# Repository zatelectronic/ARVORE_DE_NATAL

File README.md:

# ÁRVORE DE NATAL — shield de LEDs para Arduino UNO

Uma árvore de Natal desenhada na serigrafia com **12 LEDs vermelhos** de 5 mm que viram as bolinhas da árvore. A placa encaixa como **shield no Arduino UNO R3** (barra digital D2–D13 + GND) e cada LED é um pino do Arduino.

## Funcionalidades

- ✅ **Shield Arduino UNO R3** (A1) — só a barra digital D2–D13 + GND (não usa 5 V, 3,3 V nem analógicos)
- ✅ **12 LEDs 5 mm vermelhos** THT (D1–D12), um por pino digital
- ✅ **12 resistores 220 Ω 1/4 W** axiais (R1–R12), um por LED
- ✅ **Arte na serigrafia** recortada em volta de cada LED (nada de tinta sobre pad)
- ✅ Placa **100 × 100 mm**, 2 camadas, plano de GND nas duas faces

## Ligação dos LEDs

| LED | Cor | Resistor | Pino do Arduino | Corrente @ 5 V |
|---|---|---|---|---|
| D1 | vermelho | R1 220 Ω | D2 | ≈ 13,6 mA |
| D2 | vermelho | R2 220 Ω | D3 | ≈ 13,6 mA |
| D3 | vermelho | R3 220 Ω | D4 | ≈ 13,6 mA |
| D4 | vermelho | R4 220 Ω | D5 | ≈ 13,6 mA |
| D5 | vermelho | R5 220 Ω | D6 | ≈ 13,6 mA |
| D6 | vermelho | R6 220 Ω | D7 | ≈ 13,6 mA |
| D7 | vermelho | R7 220 Ω | D8 | ≈ 13,6 mA |
| D8 | vermelho | R8 220 Ω | D9 | ≈ 13,6 mA |
| D9 | vermelho | R9 220 Ω | D10 | ≈ 13,6 mA |
| D10 | vermelho | R10 220 Ω | D11 | ≈ 13,6 mA |
| D11 | vermelho | R11 220 Ω | D12 | ≈ 13,6 mA |
| D12 | vermelho | R12 220 Ω | D13 | ≈ 13,6 mA |

Cada canal: **pino → 220 Ω → LED → GND** (nível alto acende). Todos acesos ≈ **163 mA** — dentro do limite do UNO (≈ 200 mA no total), mas evite deixar os 12 acesos por muito tempo.

## Diagrama de blocos

```
┌──────────────────────┐  ARD_D2 … ARD_D13  ┌──────────────────────────┐
│  Arduino UNO R3 (A1) │ ─────────────────► │ 12 × [220 Ω → LED 5 mm]  │
│  barra D2–D13 + GND  │ ◄──────── GND ──── │  R1–R12      D1–D12      │
└──────────────────────┘                    └──────────────────────────┘
```

## Firmware

`firmware/ARVORE_DE_NATAL/ARVORE_DE_NATAL.ino` — exemplo simples (corrida, pisca alternado e aleatório).

## Esquemático (KiCad 10)

| Pág. | Folha | Conteúdo |
|---|---|---|
| 1 | Capa (A2) | blocos, mapa dos LEDs na placa, vista 3D |
| 2 | ARDUINO | A1 (shield UNO R3) + PWR_FLAG do GND |
| 3 | LEDS | D1–D12 + R1–R12 |

## Lista de materiais

| Ref. | Qtd | Valor | Footprint |
|---|---|---|---|
| A1 | 1 | Arduino UNO R3 (encaixe) | ZAT_Board_Arduino:Uno_R3_Shield_D2-D13 |
| D1–D12 | 12 | LED 5 mm vermelho | ZAT_LED:LED_D5.0mm_Red |
| R1–R12 | 12 | 220 Ω 1/4 W | ZAT_Resistor_THT:R_Axial_DIN0204_L3.6mm_D1.6mm_P7.62mm_Horizontal_220R |

## Arquivos

- `ARVORE_DE_NATAL.kicad_pro` — projeto KiCad 10 (bibliotecas globais KiCad + ZAT, sem pasta lib)
- `Zat_TitleBlock.kicad_wks` — moldura Zat Electronic
- `packages3D/` — modelos 3D usados na vista 3D

## Licença / autor

Projeto **Zat Electronic** — Kenneth Zat · Osasco/SP · hardware aberto.

*Revisão R01 — 2026-11-12 — KiCad 10.*

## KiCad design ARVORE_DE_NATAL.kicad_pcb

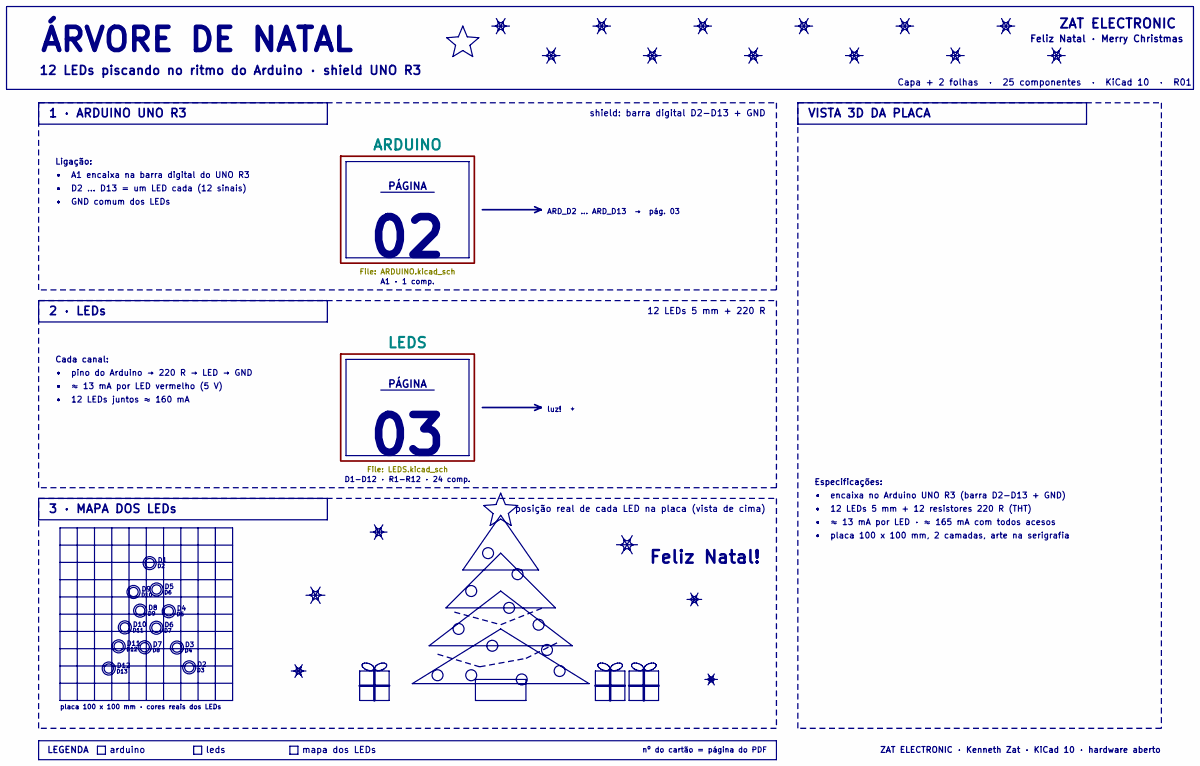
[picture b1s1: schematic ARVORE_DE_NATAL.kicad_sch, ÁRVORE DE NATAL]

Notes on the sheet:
ZAT ELECTRONIC
Especificações:
D10
ZAT ELECTRONIC · Kenneth Zat · KiCad 10 · hardware aberto
• ≈ 13 mA por LED · ≈ 165 mA com todos acesos
• 12 LEDs 5 mm + 12 resistores 220 R (THT)
1 · ARDUINO UNO R3
• D2 … D13 = um LED cada (12 sinais)
arduino
PÁGINA
nº do cartão = página do PDF
VISTA 3D DA PLACA
• ≈ 13 mA por LED vermelho (5 V)
Ligação:
D1-D12 · R1-R12 · 24 comp.
12 LEDs 5 mm + 220 R
shield: barra digital D2-D13 + GND
leds
placa 100 x 100 mm · cores reais dos LEDs
2 · LEDs
• encaixa no Arduino UNO R3 (barra D2-D13 + GND)
Capa + 2 folhas · 25 componentes · KiCad 10 · R01
Feliz Natal · Merry Christmas
• pino do Arduino → 220 R → LED → GND
D11
Cada canal:
luz! ✦
ARD_D2 … ARD_D13 → pág. 03
A1 · 1 comp.
posição real de cada LED na placa (vista de cima)
Feliz Natal!
• 12 LEDs juntos ≈ 160 mA
3 · MAPA DOS LEDs
LEGENDA
• placa 100 x 100 mm, 2 camadas, arte na serigrafia
ÁRVORE DE NATAL
mapa dos LEDs
• GND comum dos LEDs
D13
12 LEDs piscando no ritmo do Arduino · shield UNO R3

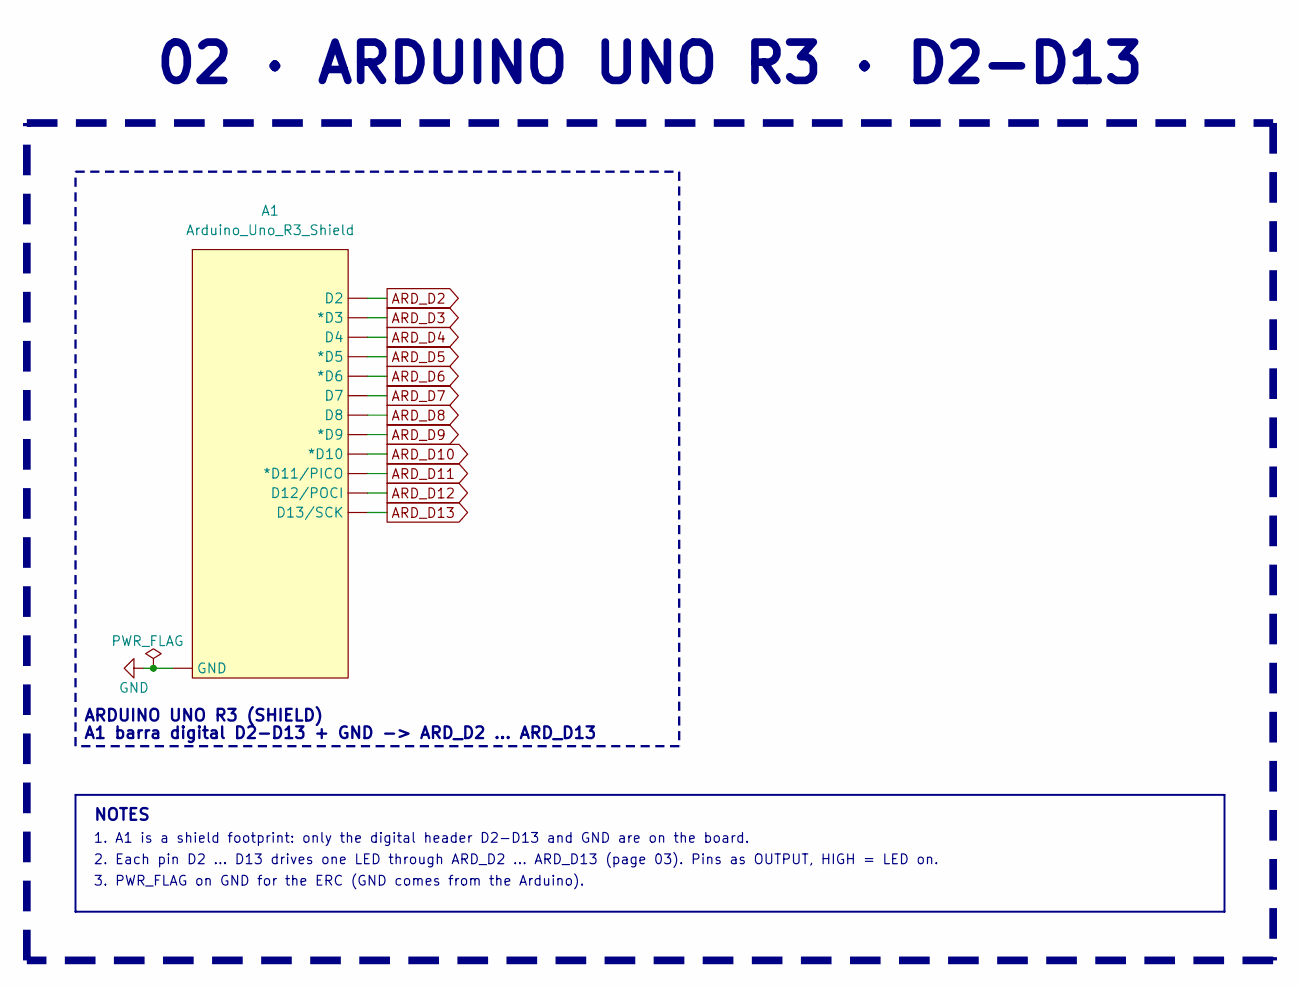
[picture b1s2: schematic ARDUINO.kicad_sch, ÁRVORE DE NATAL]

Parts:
A1: Arduino_Uno_R3_Shield; Uno_R3_Shield_D2-D13

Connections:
ARD_D2: A1.D2; also elsewhere on the board
ARD_D3: A1.D3 (*D3); also elsewhere on the board
ARD_D4: A1.D4; also elsewhere on the board
ARD_D5: A1.D5 (*D5); also elsewhere on the board
ARD_D6: A1.D6 (*D6); also elsewhere on the board
ARD_D7: A1.D7; also elsewhere on the board
ARD_D8: A1.D8; also elsewhere on the board
ARD_D9: A1.D9 (*D9); also elsewhere on the board
ARD_D10: A1.D10 (*D10); also elsewhere on the board
ARD_D11: A1.D11 (*D11/PICO); also elsewhere on the board
ARD_D12: A1.D12 (D12/POCI); also elsewhere on the board
ARD_D13: A1.D13 (D13/SCK); also elsewhere on the board
GND: A1.GND; also elsewhere on the board

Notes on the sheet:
ARDUINO UNO R3 (SHIELD)
NOTES
3. PWR_FLAG on GND for the ERC (GND comes from the Arduino).
1. A1 is a shield footprint: only the digital header D2-D13 and GND are on the board.
02 · ARDUINO UNO R3 · D2-D13
2. Each pin D2 ... D13 drives one LED through ARD_D2 ... ARD_D13 (page 03). Pins as OUTPUT, HIGH = LED on.
A1 barra digital D2-D13 + GND -> ARD_D2 ... ARD_D13

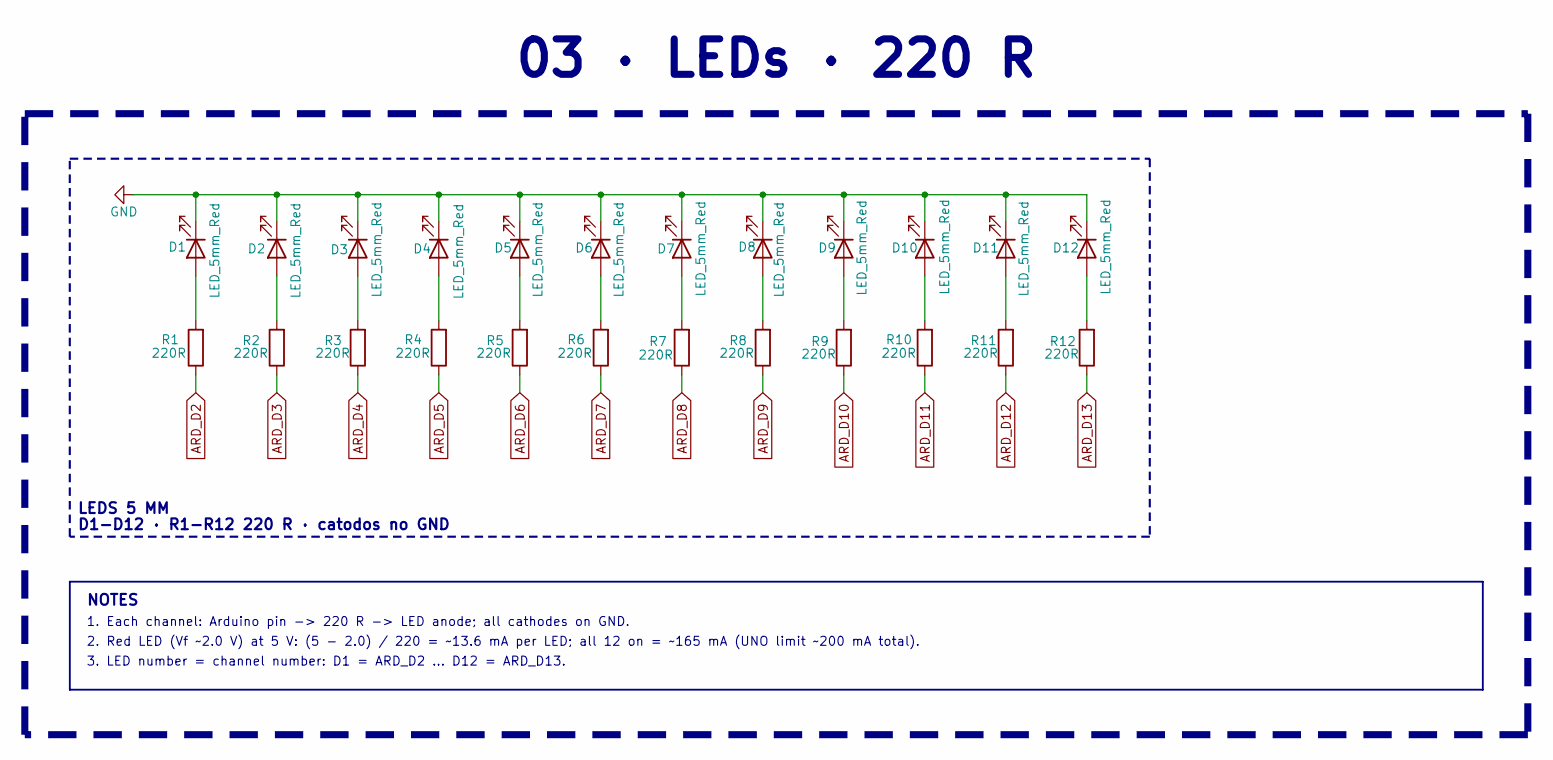
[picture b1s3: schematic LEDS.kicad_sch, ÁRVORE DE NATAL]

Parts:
D1, D2, D3, D4, D5, D6, D7, D8, D9, D10, D11, D12: LED_5mm_Red; LED_D5.0mm_Red
R1, R2, R3, R4, R5, R6, R7, R8, R9, R10, R11, R12: 220R; R_Axial_DIN0204_L3.6mm_D1.6mm_P7.62mm_Horizontal_220R

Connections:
ARD_D2: R1.1; also elsewhere on the board
ARD_D3: R2.1; also elsewhere on the board
ARD_D4: R3.1; also elsewhere on the board
ARD_D5: R4.1; also elsewhere on the board
ARD_D6: R5.1; also elsewhere on the board
ARD_D7: R6.1; also elsewhere on the board
ARD_D8: R7.1; also elsewhere on the board
ARD_D9: R8.1; also elsewhere on the board
ARD_D10: R9.1; also elsewhere on the board
ARD_D11: R10.1; also elsewhere on the board
ARD_D12: R11.1; also elsewhere on the board
ARD_D13: R12.1; also elsewhere on the board
GND: D1.1 (K), D2.1 (K), D3.1 (K), D4.1 (K), D5.1 (K), D6.1 (K), D7.1 (K), D8.1 (K), D9.1 (K), D10.1 (K), D11.1 (K), D12.1 (K); also elsewhere on the board
unnamed: D1.2 (A), R1.2
unnamed: D2.2 (A), R2.2
unnamed: D3.2 (A), R3.2
unnamed: D4.2 (A), R4.2
unnamed: D5.2 (A), R5.2
unnamed: D6.2 (A), R6.2
unnamed: D7.2 (A), R7.2
unnamed: D8.2 (A), R8.2
unnamed: D9.2 (A), R9.2
unnamed: D10.2 (A), R10.2
unnamed: D11.2 (A), R11.2
unnamed: D12.2 (A), R12.2

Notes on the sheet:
1. Each channel: Arduino pin -> 220 R -> LED anode; all cathodes on GND.
2. Red LED (Vf ~2.0 V) at 5 V: (5 - 2.0) / 220 = ~13.6 mA per LED; all 12 on = ~165 mA (UNO limit ~200 mA total).
NOTES
03 · LEDs · 220 R
D1-D12 · R1-R12 220 R · catodos no GND
3. LED number = channel number: D1 = ARD_D2 ... D12 = ARD_D13.
LEDS 5 MM

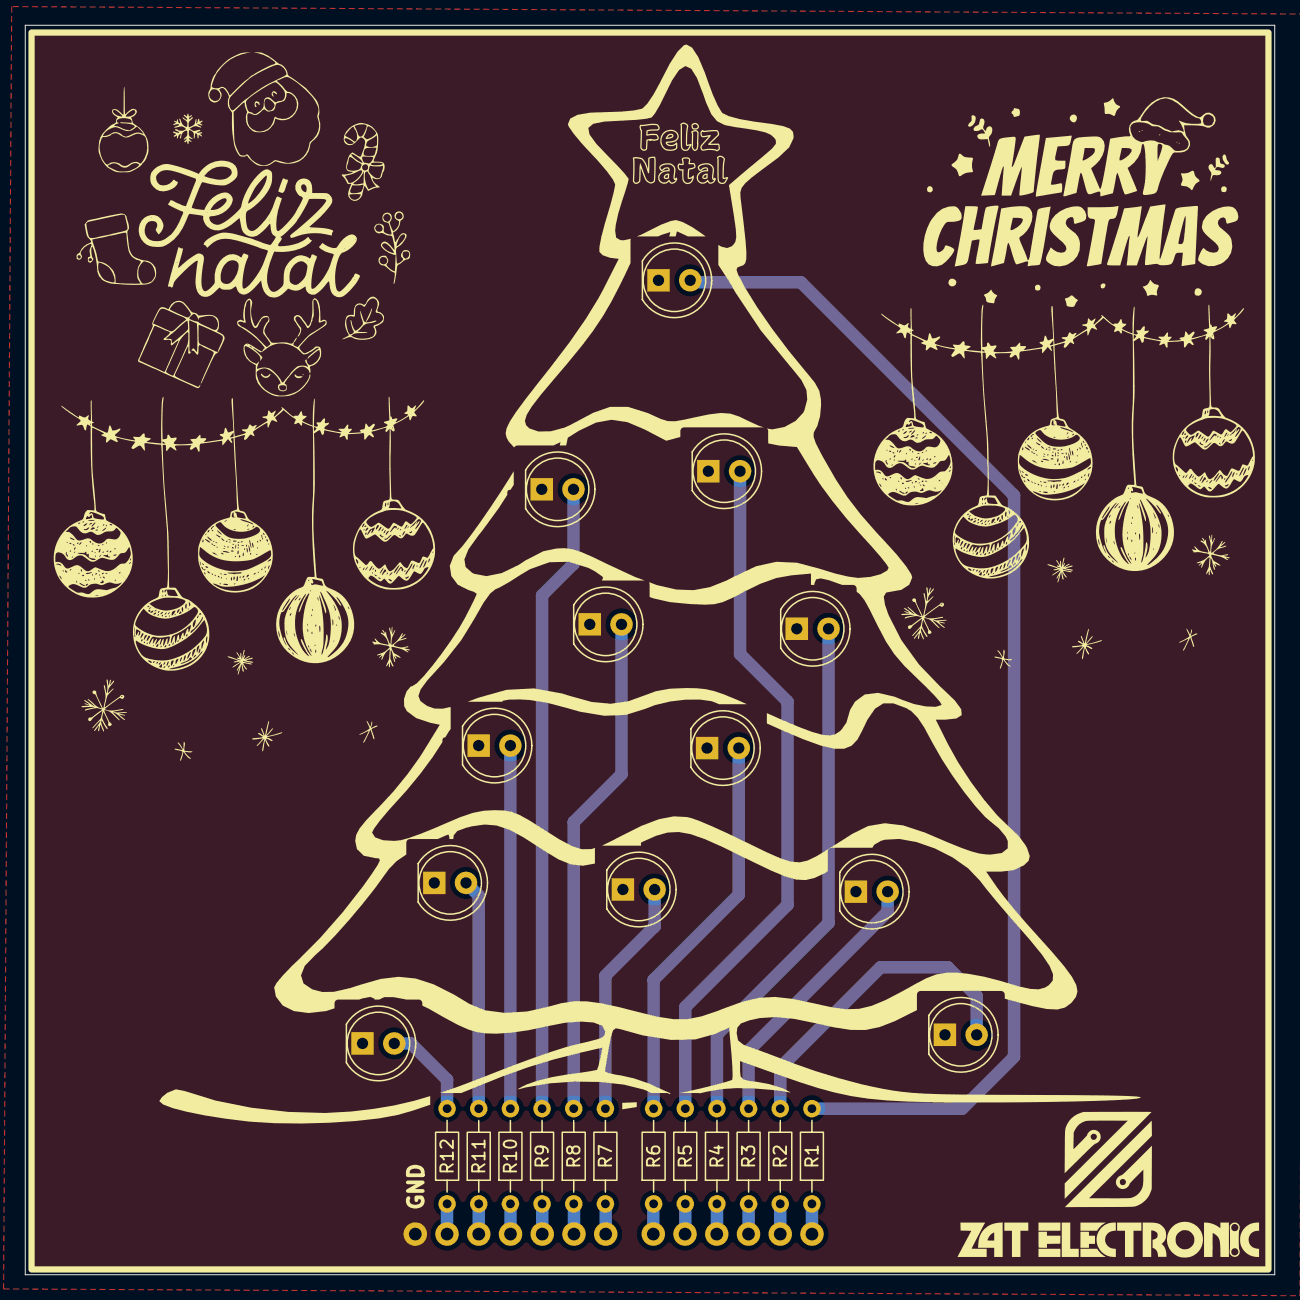
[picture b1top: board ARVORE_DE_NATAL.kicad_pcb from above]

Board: 2 copper layers, 100.0 x 100.0 mm, 25 parts (0 on the bottom side), 25 nets.

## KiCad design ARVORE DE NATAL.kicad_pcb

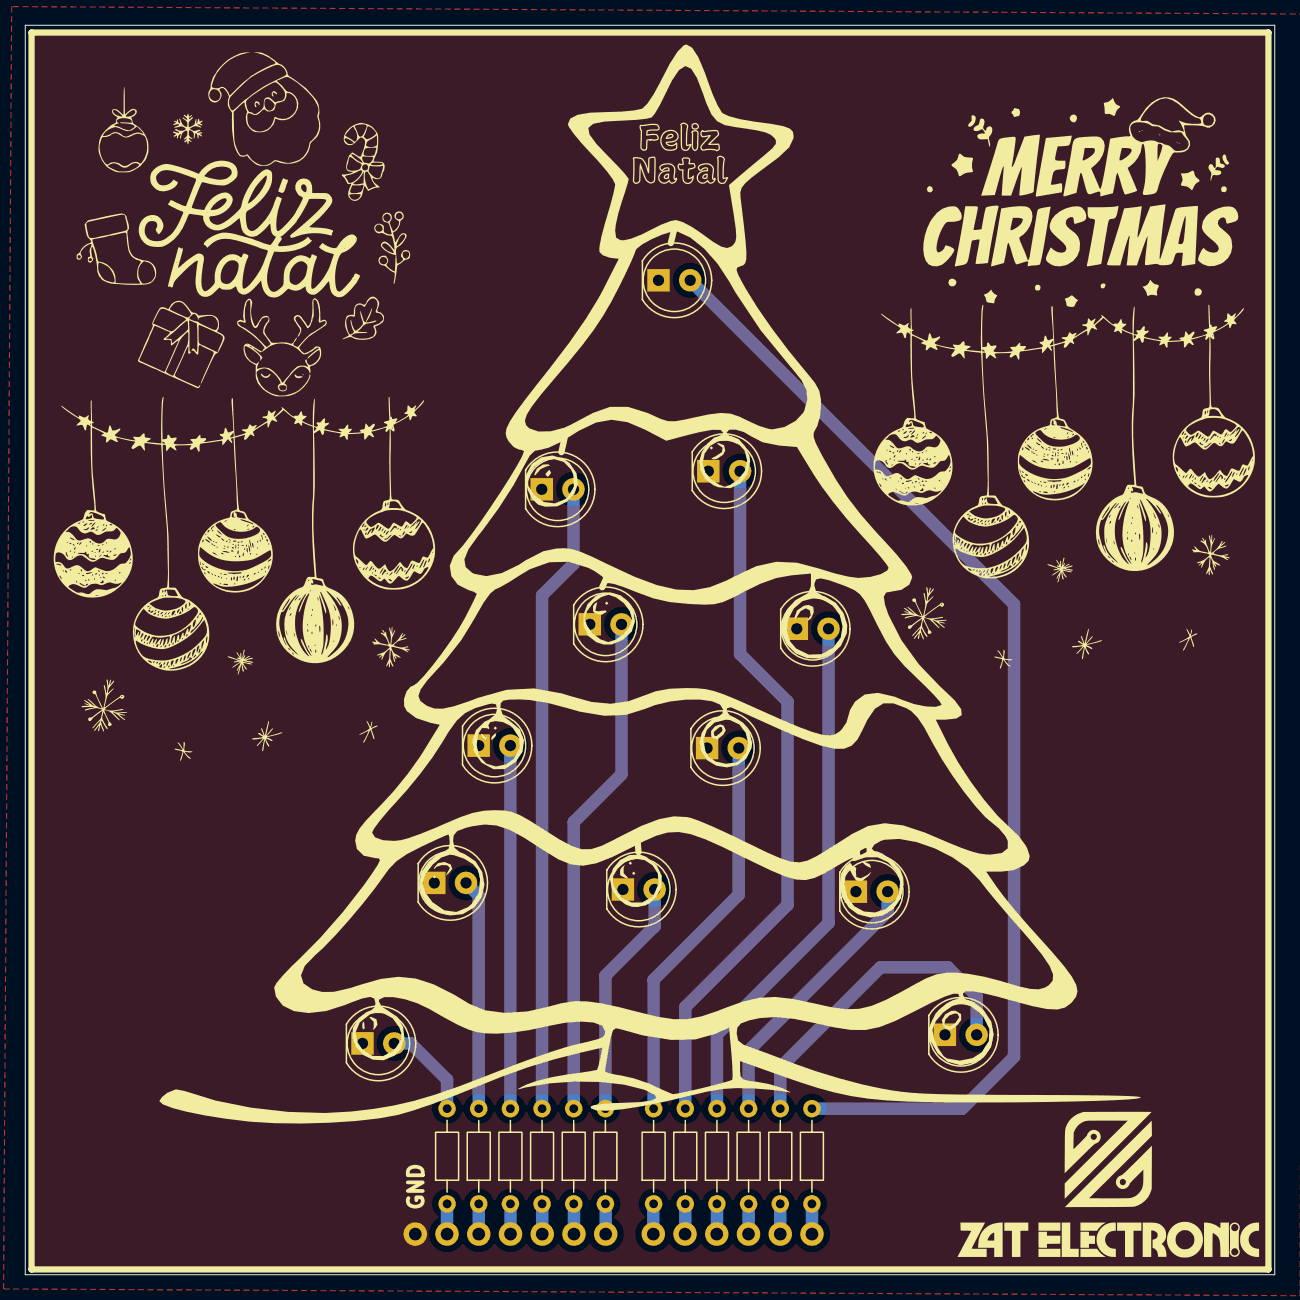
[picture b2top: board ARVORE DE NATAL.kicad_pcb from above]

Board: 2 copper layers, 100.0 x 100.0 mm, 25 parts (0 on the bottom side), 25 nets.

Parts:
B1: Arduino_Uno_R3_Shield; Uno_R3_Shield_NoLabels
L1, L2, L3, L4, L5, L6, L7, L8, L9, L10, L11, L12: LED 5MM; LED_D5.0mm
R1, R2, R3, R4, R5, R6, R7, R8, R9, R10, R11, R12: 220Ω; R_Axial_DIN0204_L3.6mm_D1.6mm_P7.62mm_Horizontal

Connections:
GND: B1.GND, L1.1 (K), L2.1 (K), L3.1 (K), L4.1 (K), L5.1 (K), L6.1 (K), L7.1 (K), L8.1 (K), L9.1 (K), L10.1 (K), L11.1 (K), L12.1 (K)
unnamed: B1.D3 (*D3), R2.1
unnamed: B1.D5 (*D5), R4.1
unnamed: B1.D6 (*D6), R5.1
unnamed: B1.D9 (*D9), R8.1
unnamed: B1.D10 (*D10), R9.1
unnamed: B1.D11 (*D11/PICO), R10.1
unnamed: B1.D12 (D12/POCI), R11.1
unnamed: B1.D13 (D13/SCK), R12.1
unnamed: B1.D2, R1.1
unnamed: B1.D4, R3.1
unnamed: B1.D7, R6.1
unnamed: B1.D8, R7.1
unnamed: L1.2 (A), R1.2
unnamed: L2.2 (A), R2.2
unnamed: L3.2 (A), R3.2
unnamed: L4.2 (A), R4.2
unnamed: L5.2 (A), R5.2
unnamed: L6.2 (A), R6.2
unnamed: L7.2 (A), R7.2
unnamed: L8.2 (A), R8.2
unnamed: L9.2 (A), R9.2
unnamed: L10.2 (A), R10.2
unnamed: L11.2 (A), R11.2
unnamed: L12.2 (A), R12.2

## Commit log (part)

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2026-06-28 COMMIT-1
